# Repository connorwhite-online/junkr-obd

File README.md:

# junkr-obd: gauge, sensors and ECU tap for a 1KZ-TE Prado

A round dash gauge (Adafruit **Qualia ESP32-S3** + 2.1" 480×480 round
display in the dead clock hole), an engine-bay sensor node, and a zero-cut
ECU interposer with a logging tap box, all on one CAN bus. Piggyback only:
the stock ECU stays in charge.

## Where the numbers come from

| Quantity | Source | Notes |
| ------ | ----- | ----- |
| EGT, pre-turbo | engine-bay node | ungrounded K-type, MAX31855 |
| Boost (absolute) + baro | engine-bay node | GM 3-bar MAP teed into the stock PIM hose |
| Boost the ECU sees, RPM, timing, fuelling, pedal | ECU tap | from the interposer |
| Coolant, ATF, intake, fuel temps, volts, lamps | ECU tap | the ECU's own sensors |

Full plan: [`docs/SENSORS_GAUGE_LOGGING.md`](docs/SENSORS_GAUGE_LOGGING.md).

Side project: a replacement climate control face with one big temperature
knob, in [`docs/CLIMATE_PANEL.md`](docs/CLIMATE_PANEL.md).

## System Block Diagram

Two MCUs, linked by CAN over a 4-pin Deutsch harness. Sensors terminate
locally on the engine-bay board (notably the K-type thermocouple — MAX31855
does cold-junction comp at its own die, so co-locating with the connector
is more accurate than running extension wire to the cabin). The cabin
Qualia is a CAN listener that updates the display.

```mermaid
flowchart LR
    subgraph EB["Engine Bay PCB"]
        direction TB
        S1["K-type EGT probe"] --> M1["MAX31855"]
        S3["GM 3-bar MAP"] --> A1["ADS1115<br/>16-bit ADC"]
        M1 -- "SPI" --> C3["ESP32-C3"]
        A1 -- "I²C" --> C3
        C3 -- "TWAI" --> X1["TJA1051<br/>(CAN xcvr)"]
        T1["120 Ω term"] -.- X1
    end
    subgraph CB["Cabin"]
        direction TB
        X2["TJA1051<br/>(CAN xcvr)"] -- "TWAI" --> Q["Qualia ESP32-S3"]
        T2["120 Ω term"] -.- X2
        Q --> D["2.1in round display<br/>Drive · Temps · Engine · Tune"]
    end
    X1 <-->|"4-pin Deutsch<br/>CAN_H / CAN_L<br/>+12 V / GND"| X2
```

## Harness Pinout (DT04-4P)

| Pin | Signal | Dir | Notes |
| --- | ------ | --- | ----- |
| 1 | +12 V (switched) | → | Fused upstream (3 A), feeds engine-bay buck |
| 2 | GND | — | Chassis ground, single-point at battery |
| 3 | CAN_H | ↔︎ | Twisted pair with CAN_L, 120 Ω term each end |
| 4 | CAN_L | ↔︎ | Twisted pair with CAN_H |

## Cabin ESP32-S3 (Qualia) Pin Map

| Function | Pin |
| -------- | --- |
| Display | Qualia RGB666 port + 40-pin ribbon (fixed by the board) |
| CAN TX (TWAI) | GPIO5 (header SCK) |
| CAN RX (TWAI) | GPIO6 (header MISO) |
| Page button (to GND) | A0 / GPIO17; the on-board DOWN button does the same |

## Engine-Bay ESP32-C3 Pin Map

(Pins chosen to avoid the SuperMini's onboard LED on GPIO8 and the boot
button on GPIO9, and the USB-Serial pins GPIO20/21.)

| Function | Pin |
| -------- | --- |
| MAX31855 SCK | GPIO4 |
| MAX31855 MISO | GPIO5 |
| MAX31855 CS | GPIO10 |
| ADS1115 A1 / A2 / A3 | MAP / spare sender / +5 V monitor (all via 2:1 dividers) |
| ADS1115 SDA | GPIO6 |
| ADS1115 SCL | GPIO7 |
| CAN TX (TWAI) | GPIO0 |
| CAN RX (TWAI) | GPIO1 |

## Calibration Constants

MAP (GM 3-bar, ratiometric): `kPa = 1.1 + 314.4 × V_sig / V_5V`, in
`src/engine_bay/map_math.h`. Baro is latched with the engine stopped.

## Power Supply

The cabin Qualia runs off USB-C (or its own switched-12 V→5 V adapter). The
engine-bay board is fed switched **12 V** through pin 1 of the Deutsch
harness, fused at ~3 A upstream, and steps it down locally with a 12 V→3.3 V
buck. Single-point ground at the battery; TVS diode on the engine-bay 12 V
input for load-dump protection.

```mermaid
flowchart LR
    BAT["12 V battery<br/>switched + 3 A fuse"] --> P1["Pin 1: +12 V"]
    GND_BAT["Chassis GND<br/>single-point @ battery"] --> P2["Pin 2: GND"]
    P1 --> TVS["TVS diode<br/>SMBJ24A"]
    TVS --> BUCK["12 V → 3.3 V<br/>buck regulator"]
    BUCK --> RAIL["3.3 V rail"]
    RAIL --> C3["ESP32-C3"]
    RAIL --> MAX["MAX31855"]
    RAIL --> ADS["ADS1115"]
    RAIL --> XCVR["TJA1051"]
    P2 --> CGND["Common GND<br/>(engine-bay board)"]
    USB["USB-C 5 V"] --> QUA["Qualia ESP32-S3<br/>(cabin)"]
```

## Bench Testing

Step-by-step bring-up guide — compile, then UI alone, then sensors alone,
then CAN loopback, then real sensors, **then** fab PCBs. See
[`docs/BENCH_TESTING.md`](docs/BENCH_TESTING.md). Bench-rig shopping
list with US suppliers: [`docs/BENCH_BOM.md`](docs/BENCH_BOM.md).

## Hardware

KiCad-ready specs for both PCBs live in [`kicad/`](kicad/) —
schematic netlists, BOMs with footprint references, design rules, and
placement/routing notes. See [`kicad/README.md`](kicad/README.md) for
the workflow.

3D models for enclosure design: [`docs/3D_MODELS.md`](docs/3D_MODELS.md)
(sourcing table + KiCad STEP-export workflow). The Qualia and ADS1115
STEP files are vendored under [`hardware/3d_models/`](hardware/3d_models/).

## Firmware Layout

One PlatformIO project; each environment picks its sources with
`build_src_filter`:

```
shared/can_protocol.h      # every CAN frame: IDs, payloads, pack/unpack
src/cabin/                 # env cabin / cabin-demo (Qualia ESP32-S3 gauge)
  gauge_state.h            #   frames -> values + alerts (pure, host-tested)
  ui.cpp                   #   LVGL pages (also runs on the PC, see below)
  display.cpp              #   Qualia RGB panel + LVGL glue
  button.h · demo.h · can_rx.cpp · main.cpp · fonts/ (Inter)
src/engine_bay/            # env engine-bay (ESP32-C3 SuperMini)
  map_math.h               #   3-bar curve + baro latch (pure, host-tested)
  sensors.cpp · can_bus.cpp · main.cpp
src/tap/                   # ECU tap box (ESP32-S3), piggyback lookup so far
src/preview/               # env gauge-preview: renders the pages to PNG
test/                      # pio test -e native
```

- **`engine-bay`** reads EGT and the 3-bar MAP, latches baro, and sends
  `0x100` EGT °F and `0x102` boost psi×10 at 20 Hz, plus `0x103` (absolute
  MAP, baro, 5 V rail, spare input) at 2 Hz. It listens for the tap's rpm
  to know when the engine is stopped. `0x101` (coolant) is retired.
- **`cabin`** listens to everything and shows five screens: Drive, Temps,
  Engine, Tune, and an Alert screen that takes over. One button pages,
  long press goes back to Drive. Without a tap box on the bus it still
  shows EGT and boost from the engine-bay node.
- **`cabin-demo`** is the same gauge fed by a built-in 90 s drive, for
  bench work with no bus.

Alert levels (pre-turbo EGT): EGT amber 1150 °F, red 1250 °F for 2 s;
coolant 221 / 230 °F; boost 15 / 17 psi; ATF 230 / 260 °F; check-engine
lamp with the engine running; battery under 12.4 V for 10 s running.

The CAN table (IDs 0x100–0x115, units, rates) is in
[`docs/SENSORS_GAUGE_LOGGING.md`](docs/SENSORS_GAUGE_LOGGING.md) §4 and,
authoritatively, in `shared/can_protocol.h`.

## Build / Flash / Test

```bash
pio run -e cabin -t upload           # gauge on CAN
pio run -e cabin-demo -t upload      # gauge with the demo drive, no bus needed
pio run -e engine-bay -t upload      # engine-bay node (engine-bay-debug prints values)
pio device monitor -e cabin

pio test -e native                   # host unit tests
pio run -e gauge-preview -t exec && python3 docs/gauge/firmware/convert.py
                                     # re-render docs/gauge/firmware/*.png
```

## ECU Interposer (in progress)

A zero-cut, printable pass-through between the KZJ95's 1KZ-TE ECU and its
harness, with an ESP32-S3 tap board that logs RPM, actual injection timing,
spill-valve fuelling, boost and temperatures. See
[`hardware/ecu_interposer/`](hardware/ecu_interposer/),
[`docs/ECU_INTERPOSER_RESEARCH.md`](docs/ECU_INTERPOSER_RESEARCH.md) and
[`docs/ECU_TAP_ARCHITECTURE.md`](docs/ECU_TAP_ARCHITECTURE.md).

### Learning tuner (simulation stage)

`tuner/` is a Python package that learns piggyback correction maps
(PIM and coolant-temp offsets over baro × intake temp × rpm × pedal) from
drive logs, with optional sensor modules (wideband, EGT, baro, GPS, IMU,
fuel flow) that unlock more authority. `src/tap/piggyback.h` is the
matching firmware lookup and safety caps. See
[`docs/LEARNING_TUNER.md`](docs/LEARNING_TUNER.md).

```
python -m tuner campaign --rounds 15 --drives 4
python -m unittest discover -s tuner/tests -t .
```

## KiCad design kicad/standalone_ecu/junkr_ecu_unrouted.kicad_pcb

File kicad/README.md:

# KiCad Hardware Designs

Three PCBs:

- **`engine_bay/`** — the 12 V-tolerant board that lives next to the
  sensors. Mounts the ESP32-C3 SuperMini, MAX31855 breakout, ADS1115
  breakout, and TJA1051 CAN transceiver on 0.1″ headers. Adds power
  conditioning (reverse-polarity diode, TVS, polyfuse, dual buck
  regulators for 3.3 V + 5 V rails), CAN bus termination, and the
  signal-conditioning network for the NTC and MAP sensors.

- **`cabin/`** — a small breakout that pairs with the Qualia ESP32-S3.
  Carries only the TJA1051 transceiver, 120 Ω termination jumper, and
  the Deutsch plug. Connects to the Qualia over a short 4-wire flex
  (3.3 V, GND, TWAI_TX, TWAI_RX).

- **`tap/`** — the ESP32-S3 board in the ECU interposer's tap box. Reads
  the stock ECU's sensors, switches and pulse lines through 47 kΩ splice
  resistors (VR, ADC and Schmitt front ends), logs to microSD and joins
  the CAN bus. Phase 2 parts (DAC + fail-to-stock relays) are optional.
  `frontend_check.py` checks every front-end value.

## How to use this

Each board has three deliverables in its directory:

| File | What it is |
| ---- | ---------- |
| `schematic.md` | Net-by-net wiring. Use this as the canonical reference when capturing the schematic in KiCad — every net and every pin is listed. |
| `bom.csv` | The exact parts with KiCad symbol + footprint library references. Import into KiCad's symbol-to-footprint assigner (`cvpcb`). |
| `notes.md` | Placement strategy, routing constraints, manufacturing notes, design checks. |

Shared design rules — trace widths, copper pours, layer stack, clearances,
DRC settings — live in [`DESIGN_RULES.md`](DESIGN_RULES.md).

## KiCad workflow

1. `File → New → Project` inside each board's directory. Name the project
   `junkr-engine-bay` and `junkr-cabin` respectively.
2. In Schematic Editor: add symbols per `schematic.md`. Use only symbols
   from KiCad's stock libraries (referenced by name in the BOM) — no
   custom libraries needed for revision 1.
3. Run ERC. Resolve any unconnected pin warnings using the “No-connect”
   flag where the BOM marks pins as NC.
4. Open `cvpcb` (Tools → Assign Footprints), assign per the BOM's
   `footprint` column.
5. Push to PCB Editor (`Tools → Update PCB from Schematic`).
6. Apply board outline + mounting hole positions per `notes.md`.
7. Place components per the zones described in `notes.md`.
8. Set design rules per `DESIGN_RULES.md`, then route (manual or
   Freerouting).

## Why not generated `.kicad_sch` files

KiCad's schematic format embeds UUIDs and references that depend on the
local KiCad library paths. Generating them blind tends to produce files
that won't open cleanly. The netlist tables in `schematic.md` carry the
same information in a form you can act on in 20–30 minutes per board in
the KiCad GUI, with much lower risk of broken-project regrets.

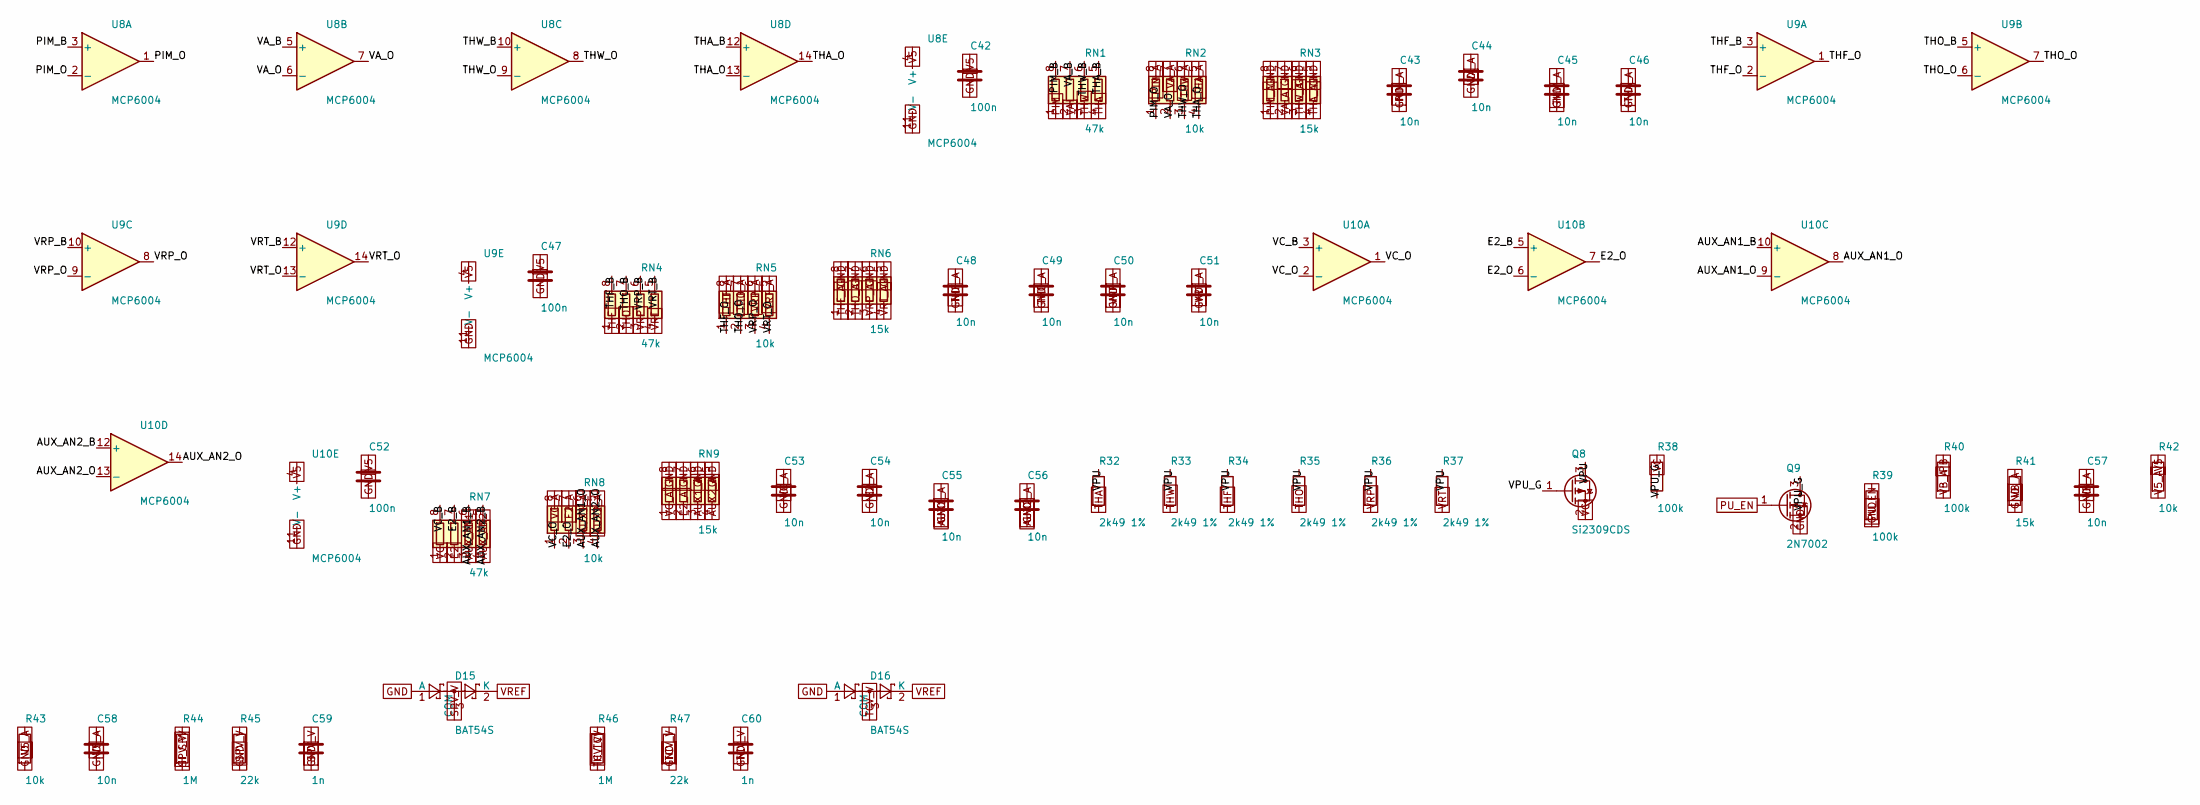
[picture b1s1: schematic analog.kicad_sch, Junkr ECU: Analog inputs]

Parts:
C42, C47, C52: 100n; C_0603_1608Metric
C43, C44, C45, C46, C48, C49, C50, C51, C53, C54, C55, C56, C57, C58: 10n; C_0603_1608Metric
C59, C60: 1n; C_0603_1608Metric
D15, D16: BAT54S; SOT-23; MPN BAT54S
Q8: Si2309CDS; SOT-23; MPN SI2309CDS-T1-GE3
Q9: 2N7002; SOT-23; MPN 2N7002
R32, R33, R34, R35, R36, R37: 2k49 1%; R_0603_1608Metric
R38, R39, R40: 100k; R_0603_1608Metric
R41: 15k; R_0603_1608Metric
R42, R43: 10k; R_0603_1608Metric
R44, R46: 1M; R_0603_1608Metric
R45, R47: 22k; R_0603_1608Metric
RN1, RN4, RN7: 47k; R_Array_Convex_4x0603
RN2, RN5, RN8: 10k; R_Array_Convex_4x0603
RN3, RN6, RN9: 15k; R_Array_Convex_4x0603
U8, U9, U10: MCP6004; SOIC-14_3.9x8.7mm_P1.27mm; MPN MCP6004T-I/SL

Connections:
AUX1_A: C55.1, RN8.6 (R3.2), RN9.3 (R3.1); also elsewhere on the board
AUX2_A: C56.1, RN8.5 (R4.2), RN9.4 (R4.1); also elsewhere on the board
AUX_AN1: RN7.3 (R3.1); also elsewhere on the board
AUX_AN1_B: RN7.6 (R3.2), U10.10 (+)
AUX_AN1_O: RN8.3 (R3.1), U10.8, U10.9 (-)
AUX_AN2: RN7.4 (R4.1); also elsewhere on the board
AUX_AN2_B: RN7.5 (R4.2), U10.12 (+)
AUX_AN2_O: RN8.4 (R4.1), U10.13 (-), U10.14
E2: RN7.2 (R2.1); also elsewhere on the board
E2_A: C54.1, RN8.7 (R2.2), RN9.2 (R2.1); also elsewhere on the board
E2_B: RN7.7 (R2.2), U10.5 (+)
E2_O: RN8.2 (R2.1), U10.6 (-), U10.7
GND: C42.2, C43.2, C44.2, C45.2, C46.2, C47.2, C48.2, C49.2, C50.2, C51.2, C52.2, C53.2, C54.2, C55.2, C56.2, C57.2, C58.2, C59.2, C60.2, D15.1 (A), D16.1 (A), Q9.2 (S), R39.2, R41.2, R43.2, R45.2, R47.2, RN3.5 (R4.2), RN3.6 (R3.2), RN3.7 (R2.2), RN3.8 (R1.2), RN6.5 (R4.2), RN6.6 (R3.2), RN6.7 (R2.2), RN6.8 (R1.2), RN9.5 (R4.2), RN9.6 (R3.2), RN9.7 (R2.2), RN9.8 (R1.2), U8.11 (V-), U9.11 (V-), U10.11 (V-); also elsewhere on the board
H_SPV: R44.1; also elsewhere on the board
H_TCV: R46.1; also elsewhere on the board
PB: R40.1; also elsewhere on the board
PIM: RN1.1 (R1.1); also elsewhere on the board
PIM_A: C43.1, RN2.8 (R1.2), RN3.1 (R1.1); also elsewhere on the board
PIM_B: RN1.8 (R1.2), U8.3 (+)
PIM_O: RN2.1 (R1.1), U8.1, U8.2 (-)
PU_EN: Q9.1 (G), R39.1; also elsewhere on the board
SPV_V: C59.1, D15.3 (COM), R44.2, R45.1; also elsewhere on the board
TCV_V: C60.1, D16.3 (COM), R46.2, R47.1; also elsewhere on the board
THA: R32.2, RN1.4 (R4.1); also elsewhere on the board
THA_A: C46.1, RN2.5 (R4.2), RN3.4 (R4.1); also elsewhere on the board
THA_B: RN1.5 (R4.2), U8.12 (+)
THA_O: RN2.4 (R4.1), U8.13 (-), U8.14
THF: R34.2, RN4.1 (R1.1); also elsewhere on the board
THF_A: C48.1, RN5.8 (R1.2), RN6.1 (R1.1); also elsewhere on the board
THF_B: RN4.8 (R1.2), U9.3 (+)
THF_O: RN5.1 (R1.1), U9.1, U9.2 (-)
THO: R35.2, RN4.2 (R2.1); also elsewhere on the board
THO_A: C49.1, RN5.7 (R2.2), RN6.2 (R2.1); also elsewhere on the board
THO_B: RN4.7 (R2.2), U9.5 (+)
THO_O: RN5.2 (R2.1), U9.6 (-), U9.7
THW: R33.2, RN1.3 (R3.1); also elsewhere on the board
THW_A: C45.1, RN2.6 (R3.2), RN3.3 (R3.1); also elsewhere on the board
THW_B: RN1.6 (R3.2), U8.10 (+)
THW_O: RN2.3 (R3.1), U8.8, U8.9 (-)
V5: C42.1, C47.1, C52.1, R42.1, U8.4 (V+), U9.4 (V+), U10.4 (V+); also elsewhere on the board
V5_A: C58.1, R42.2, R43.1; also elsewhere on the board
VA: RN1.2 (R2.1); also elsewhere on the board
VA_A: C44.1, RN2.7 (R2.2), RN3.2 (R2.1); also elsewhere on the board
VA_B: RN1.7 (R2.2), U8.5 (+)
VA_O: RN2.2 (R2.1), U8.6 (-), U8.7
VB_A: C57.1, R40.2, R41.1; also elsewhere on the board
VC: Q8.2 (S), R38.1, RN7.1 (R1.1); also elsewhere on the board
VC_A: C53.1, RN8.8 (R1.2), RN9.1 (R1.1); also elsewhere on the board
VC_B: RN7.8 (R1.2), U10.3 (+)
VC_O: RN8.1 (R1.1), U10.1, U10.2 (-)
VPU: Q8.3 (D), R32.1, R33.1, R34.1, R35.1, R36.1, R37.1
VPU_G: Q8.1 (G), Q9.3 (D), R38.2
VREF: D15.2 (K), D16.2 (K); also elsewhere on the board
VRP: R36.2, RN4.3 (R3.1); also elsewhere on the board
VRP_A: C50.1, RN5.6 (R3.2), RN6.3 (R3.1); also elsewhere on the board
VRP_B: RN4.6 (R3.2), U9.10 (+)
VRP_O: RN5.3 (R3.1), U9.8, U9.9 (-)
VRT: R37.2, RN4.4 (R4.1); also elsewhere on the board
VRT_A: C51.1, RN5.5 (R4.2), RN6.4 (R4.1); also elsewhere on the board
VRT_B: RN4.5 (R4.2), U9.12 (+)
VRT_O: RN5.4 (R4.1), U9.13 (-), U9.14

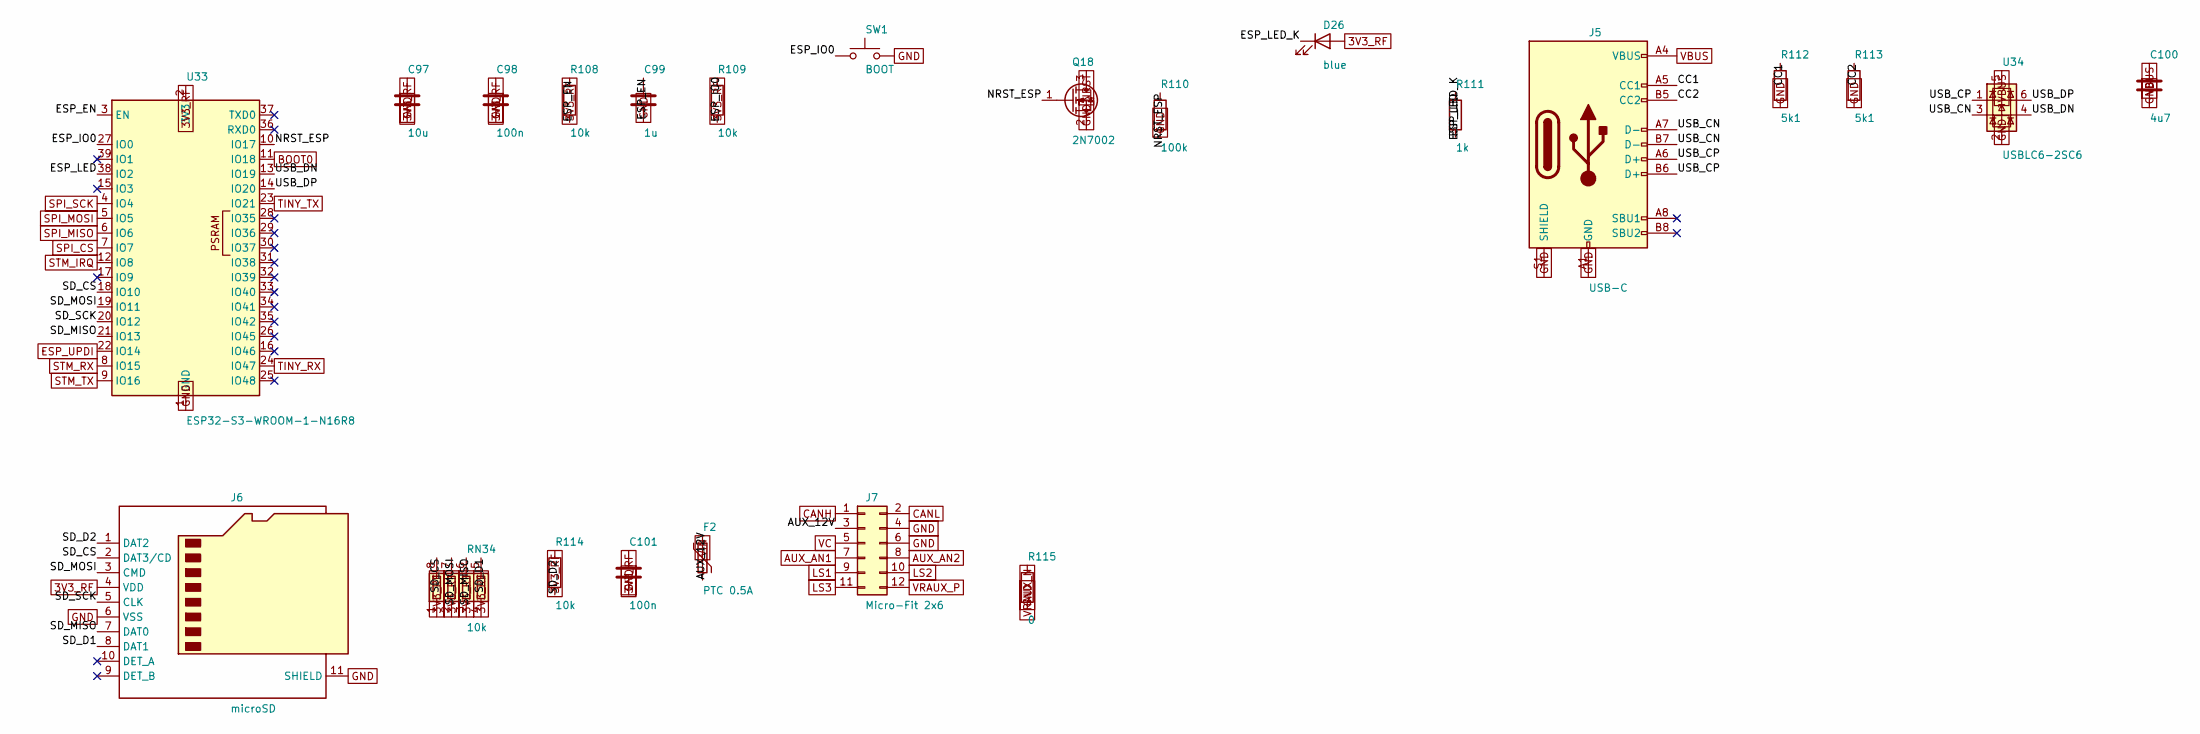
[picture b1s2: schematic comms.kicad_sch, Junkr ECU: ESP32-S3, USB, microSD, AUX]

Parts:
C97: 10u; C_0805_2012Metric
C98, C101: 100n; C_0603_1608Metric
C99: 1u; C_0603_1608Metric
C100: 4u7; C_0805_2012Metric
D26: blue; LED_0603_1608Metric
F2: PTC 0.5A; Fuse_1812_4532Metric; MPN 1812L050/30PR
J5: USB-C; USB_C_Receptacle_HRO_TYPE-C-31-M-12; MPN TYPE-C-31-M-12
J6: microSD; microSD_HC_Hirose_DM3AT-SF-PEJM5; MPN DM3AT-SF-PEJM5
J7: Micro-Fit 2x6; Molex_Micro-Fit_3.0_43045-1212_2x06_P3.00mm_Vertical; MPN 43045-1212
Q18: 2N7002; SOT-23; MPN 2N7002
R108, R109, R114: 10k; R_0603_1608Metric
R110: 100k; R_0603_1608Metric
R111: 1k; R_0603_1608Metric
R112, R113: 5k1; R_0603_1608Metric
R115: 0; R_0603_1608Metric
RN34: 10k; R_Array_Convex_4x0603
SW1: BOOT; SW_SPST_PTS810
U33: ESP32-S3-WROOM-1-N16R8; ESP32-S3-WROOM-1; MPN ESP32-S3-WROOM-1-N16R8
U34: USBLC6-2SC6; SOT-23-6; MPN USBLC6-2SC6

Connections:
3V3_RF: C97.1, C98.1, C101.1, D26.2 (A), J6.4 (VDD), R108.1, R109.1, R114.1, RN34.1 (R1.1), RN34.2 (R2.1), RN34.3 (R3.1), RN34.4 (R4.1), U33.2 (3V3); also elsewhere on the board
AUX_12V: F2.2, J7.3
AUX_AN1: J7.7; also elsewhere on the board
AUX_AN2: J7.8; also elsewhere on the board
BOOT0: U33.11 (IO18); also elsewhere on the board
CANH: J7.1; also elsewhere on the board
CANL: J7.2; also elsewhere on the board
CC1: J5.A5 (CC1), R112.1
CC2: J5.B5 (CC2), R113.1
ESP_EN: C99.1, R108.2, U33.3 (EN)
ESP_IO0: R109.2, SW1.1, U33.27 (IO0)
ESP_LED: R111.1, U33.38 (IO2)
ESP_LED_K: D26.1 (K), R111.2
ESP_UPDI: U33.22 (IO14); also elsewhere on the board
GND: C97.2, C98.2, C99.2, C100.2, C101.2, J5.A1 (GND), J5.A12 (GND), J5.B1 (GND), J5.B12 (GND), J5.S1 (SHIELD), J6.6 (VSS), J6.11 (SHIELD), J7.4, J7.6, Q18.2 (S), R110.2, R112.2, R113.2, R115.2, SW1.2, U33.1 (GND), U33.40 (GND), U33.41 (GND), U34.2 (GND); also elsewhere on the board
LS1: J7.9; also elsewhere on the board
LS2: J7.10; also elsewhere on the board
LS3: J7.11; also elsewhere on the board
NRST: Q18.3 (D); also elsewhere on the board
NRST_ESP: Q18.1 (G), R110.1, U33.10 (IO17)
SD_CS: J6.2 (DAT3/CD), RN34.8 (R1.2), U33.18 (IO10)
SD_D1: J6.8 (DAT1), RN34.5 (R4.2)
SD_D2: J6.1 (DAT2), R114.2
SD_MISO: J6.7 (DAT0), RN34.6 (R3.2), U33.21 (IO13)
SD_MOSI: J6.3 (CMD), RN34.7 (R2.2), U33.19 (IO11)
SD_SCK: J6.5 (CLK), U33.20 (IO12)
SPI_CS: U33.7 (IO7); also elsewhere on the board
SPI_MISO: U33.6 (IO6); also elsewhere on the board
SPI_MOSI: U33.5 (IO5); also elsewhere on the board
SPI_SCK: U33.4 (IO4); also elsewhere on the board
STM_IRQ: U33.12 (IO8); also elsewhere on the board
STM_RX: U33.8 (IO15); also elsewhere on the board
STM_TX: U33.9 (IO16); also elsewhere on the board
TINY_RX: U33.24 (IO47); also elsewhere on the board
TINY_TX: U33.23 (IO21); also elsewhere on the board
USB_CN: J5.A7 (D-), J5.B7 (D-), U34.3 (I/O2)
USB_CP: J5.A6 (D+), J5.B6 (D+), U34.1 (I/O1)
USB_DN: U33.13 (IO19), U34.4 (I/O2)
USB_DP: U33.14 (IO20), U34.6 (I/O1)
VBUS: C100.1, J5.A4 (VBUS), J5.A9 (VBUS), J5.B4 (VBUS), J5.B9 (VBUS), U34.5 (VBUS); also elsewhere on the board
VC: J7.5; also elsewhere on the board
VIN: F2.1; also elsewhere on the board
VRAUX_N: R115.1; also elsewhere on the board
VRAUX_P: J7.12; also elsewhere on the board

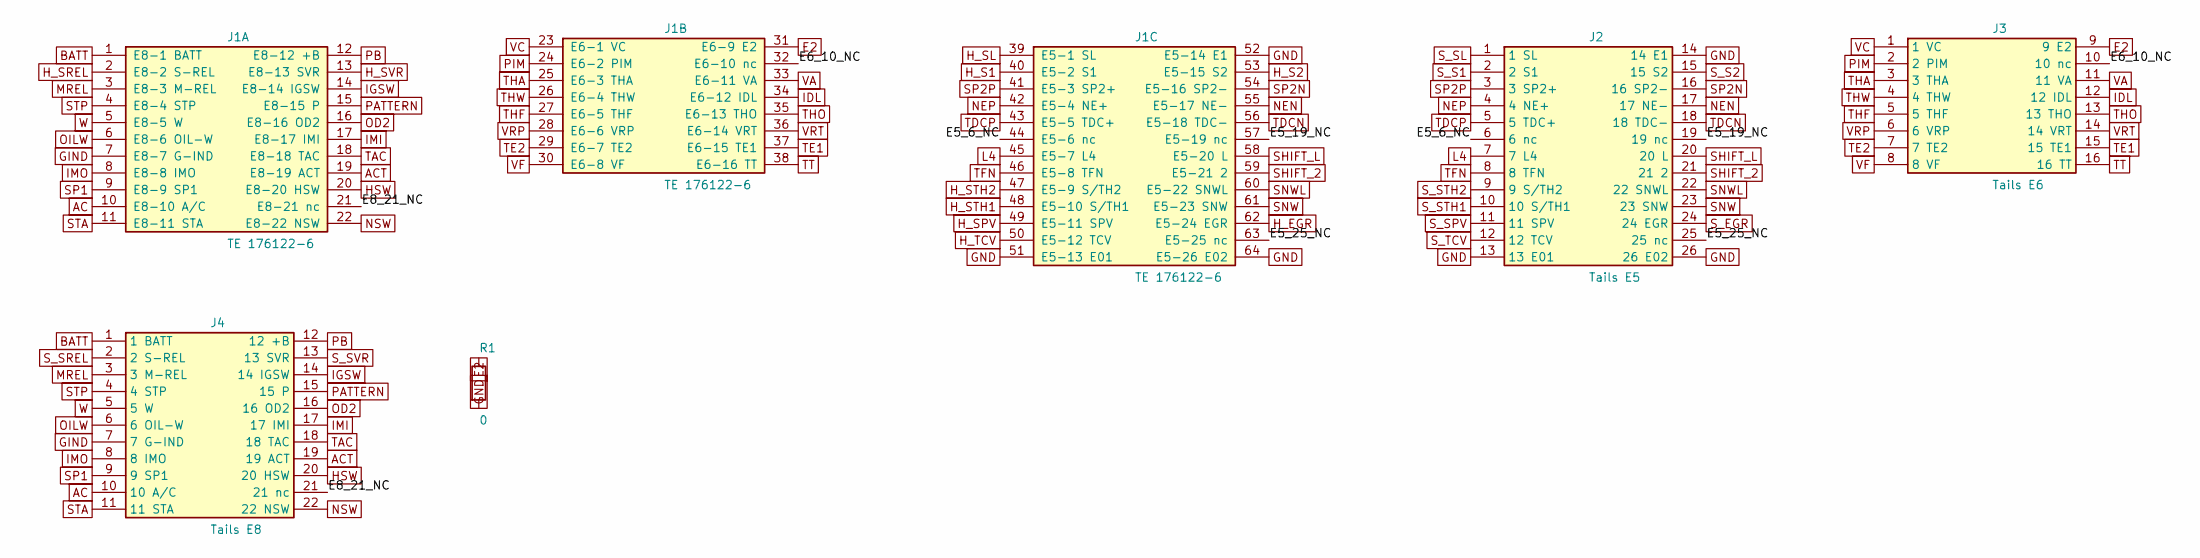
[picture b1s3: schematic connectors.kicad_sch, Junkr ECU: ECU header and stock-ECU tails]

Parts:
J1: TE 176122-6; TE_176122-6_RA; MPN 176122-6
J2: Tails E5; Tails_E5
J3: Tails E6; Tails_E6
J4: Tails E8; Tails_E8
R1: 0; R_0603_1608Metric

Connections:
AC: J1.10 (E8-10 A/C), J4.10 (10 A/C); also elsewhere on the board
ACT: J1.19 (E8-19 ACT), J4.19 (19 ACT); also elsewhere on the board
BATT: J1.1 (E8-1 BATT), J4.1 (1 BATT); also elsewhere on the board
E2: J1.31 (E6-9 E2), J3.9 (9 E2), R1.1; also elsewhere on the board
E5_6_NC: J1.44 (E5-6 nc), J2.6 (6 nc)
E5_19_NC: J1.57 (E5-19 nc), J2.19 (19 nc)
E5_25_NC: J1.63 (E5-25 nc), J2.25 (25 nc)
E6_10_NC: J1.32 (E6-10 nc), J3.10 (10 nc)
E8_21_NC: J1.21 (E8-21 nc), J4.21 (21 nc)
GIND: J1.7 (E8-7 G-IND), J4.7 (7 G-IND); also elsewhere on the board
GND: J1.51 (E5-13 E01), J1.52 (E5-14 E1), J1.64 (E5-26 E02), J2.13 (13 E01), J2.14 (14 E1), J2.26 (26 E02), R1.2; also elsewhere on the board
HSW: J1.20 (E8-20 HSW), J4.20 (20 HSW); also elsewhere on the board
H_EGR: J1.62 (E5-24 EGR); also elsewhere on the board
H_S1: J1.40 (E5-2 S1); also elsewhere on the board
H_S2: J1.53 (E5-15 S2); also elsewhere on the board
H_SL: J1.39 (E5-1 SL); also elsewhere on the board
H_SPV: J1.49 (E5-11 SPV); also elsewhere on the board
H_SREL: J1.2 (E8-2 S-REL); also elsewhere on the board
H_STH1: J1.48 (E5-10 S/TH1); also elsewhere on the board
H_STH2: J1.47 (E5-9 S/TH2); also elsewhere on the board
H_SVR: J1.13 (E8-13 SVR); also elsewhere on the board
H_TCV: J1.50 (E5-12 TCV); also elsewhere on the board
IDL: J1.34 (E6-12 IDL), J3.12 (12 IDL); also elsewhere on the board
IGSW: J1.14 (E8-14 IGSW), J4.14 (14 IGSW); also elsewhere on the board
IMI: J1.17 (E8-17 IMI), J4.17 (17 IMI); also elsewhere on the board
IMO: J1.8 (E8-8 IMO), J4.8 (8 IMO); also elsewhere on the board
L4: J1.45 (E5-7 L4), J2.7 (7 L4); also elsewhere on the board
MREL: J1.3 (E8-3 M-REL), J4.3 (3 M-REL); also elsewhere on the board
NEN: J1.55 (E5-17 NE-), J2.17 (17 NE-); also elsewhere on the board
NEP: J1.42 (E5-4 NE+), J2.4 (4 NE+); also elsewhere on the board
NSW: J1.22 (E8-22 NSW), J4.22 (22 NSW); also elsewhere on the board
OD2: J1.16 (E8-16 OD2), J4.16 (16 OD2); also elsewhere on the board
OILW: J1.6 (E8-6 OIL-W), J4.6 (6 OIL-W); also elsewhere on the board
PATTERN: J1.15 (E8-15 P), J4.15 (15 P); also elsewhere on the board
PB: J1.12 (E8-12 +B), J4.12 (12 +B); also elsewhere on the board
PIM: J1.24 (E6-2 PIM), J3.2 (2 PIM); also elsewhere on the board
SHIFT_2: J1.59 (E5-21 2), J2.21 (21 2); also elsewhere on the board
SHIFT_L: J1.58 (E5-20 L), J2.20 (20 L); also elsewhere on the board
SNW: J1.61 (E5-23 SNW), J2.23 (23 SNW); also elsewhere on the board
SNWL: J1.60 (E5-22 SNWL), J2.22 (22 SNWL); also elsewhere on the board
SP1: J1.9 (E8-9 SP1), J4.9 (9 SP1); also elsewhere on the board
SP2N: J1.54 (E5-16 SP2-), J2.16 (16 SP2-); also elsewhere on the board
SP2P: J1.41 (E5-3 SP2+), J2.3 (3 SP2+); also elsewhere on the board
STA: J1.11 (E8-11 STA), J4.11 (11 STA); also elsewhere on the board
STP: J1.4 (E8-4 STP), J4.4 (4 STP); also elsewhere on the board
S_EGR: J2.24 (24 EGR); also elsewhere on the board
S_S1: J2.2 (2 S1); also elsewhere on the board
S_S2: J2.15 (15 S2); also elsewhere on the board
S_SL: J2.1 (1 SL); also elsewhere on the board
S_SPV: J2.11 (11 SPV); also elsewhere on the board
S_SREL: J4.2 (2 S-REL); also elsewhere on the board
S_STH1: J2.10 (10 S/TH1); also elsewhere on the board
S_STH2: J2.9 (9 S/TH2); also elsewhere on the board
S_SVR: J4.13 (13 SVR); also elsewhere on the board
S_TCV: J2.12 (12 TCV); also elsewhere on the board
TAC: J1.18 (E8-18 TAC), J4.18 (18 TAC); also elsewhere on the board
TDCN: J1.56 (E5-18 TDC-), J2.18 (18 TDC-); also elsewhere on the board
TDCP: J1.43 (E5-5 TDC+), J2.5 (5 TDC+); also elsewhere on the board
TE1: J1.37 (E6-15 TE1), J3.15 (15 TE1); also elsewhere on the board
TE2: J1.29 (E6-7 TE2), J3.7 (7 TE2); also elsewhere on the board
TFN: J1.46 (E5-8 TFN), J2.8 (8 TFN); also elsewhere on the board
THA: J1.25 (E6-3 THA), J3.3 (3 THA); also elsewhere on the board
THF: J1.27 (E6-5 THF), J3.5 (5 THF); also elsewhere on the board
THO: J1.35 (E6-13 THO), J3.13 (13 THO); also elsewhere on the board
THW: J1.26 (E6-4 THW), J3.4 (4 THW); also elsewhere on the board
TT: J1.38 (E6-16 TT), J3.16 (16 TT); also elsewhere on the board
VA: J1.33 (E6-11 VA), J3.11 (11 VA); also elsewhere on the board
VC: J1.23 (E6-1 VC), J3.1 (1 VC); also elsewhere on the board
VF: J1.30 (E6-8 VF), J3.8 (8 VF); also elsewhere on the board
VRP: J1.28 (E6-6 VRP), J3.6 (6 VRP); also elsewhere on the board
VRT: J1.36 (E6-14 VRT), J3.14 (14 VRT); also elsewhere on the board
W: J1.5 (E8-5 W), J4.5 (5 W); also elsewhere on the board
